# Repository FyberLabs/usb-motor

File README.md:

# usb-motor driver
Variation on the [Small Multicell USB Type C Charger](https://hackaday.io/project/85465-small-multicell-usb-type-c-charger), but with a specific purpose of making USB powered tools.
There will be a brushless version eventually and a few other application variations.
It supports a variety of rechargeable batteries and 1-4 cells depending on the solder bridge configuration.

For right now it has a single power/action button that can turn on/off, change speed, and reverse direction.
A capacitive trigger or other more precise control can be added.
There is also a reset button that can be removed after development.

These boards should 'mostly' stack in a 1x1.5" space with only a few wiring problems between them.
This design has excessive FET control and filtering which can be reduced.
Ideally, the design should fit on a single 1x1.5" board when developed for a specific application.

[Submitted gerbers to oshpark](https://oshpark.com/shared_projects/w56T8NJs])

[Assembly BOM](http://htmlpreview.github.com/?https://github.com/FyberLabs/usb-motor/blob/master/bom/ibom.html)
Generated By [InteractiveHtmlBom](https://github.com/openscopeproject/InteractiveHtmlBom)  

GPL licensed firmware will be coming for the CCG3.  I expect to use stock TI firmware for TI chips.

Notes:
* There will be bugs in the hardware and eventually they will hopefully be found and 'fixed.
* There are many solderbridges to disable FET controls and select cell counts as necessary.
* The CC 5V line on CCG3 should be routed or the 3v3 supply made 5V to fully enable a powerbank/OTG capabilities.
* Initial testing of some of the boards, so some logic may be incorrect.
* Developed with extra small designator silkscreen fonts which are likely to fail most PCB processes.  
(They are not that important to my build process, and usually make a mess of the silkscreen either way.)
* First panel attempted through oshpark  
(Usually I remove edge lines on mousebites for other fabs, though this variation does make copper zones in KiCAD work better.)

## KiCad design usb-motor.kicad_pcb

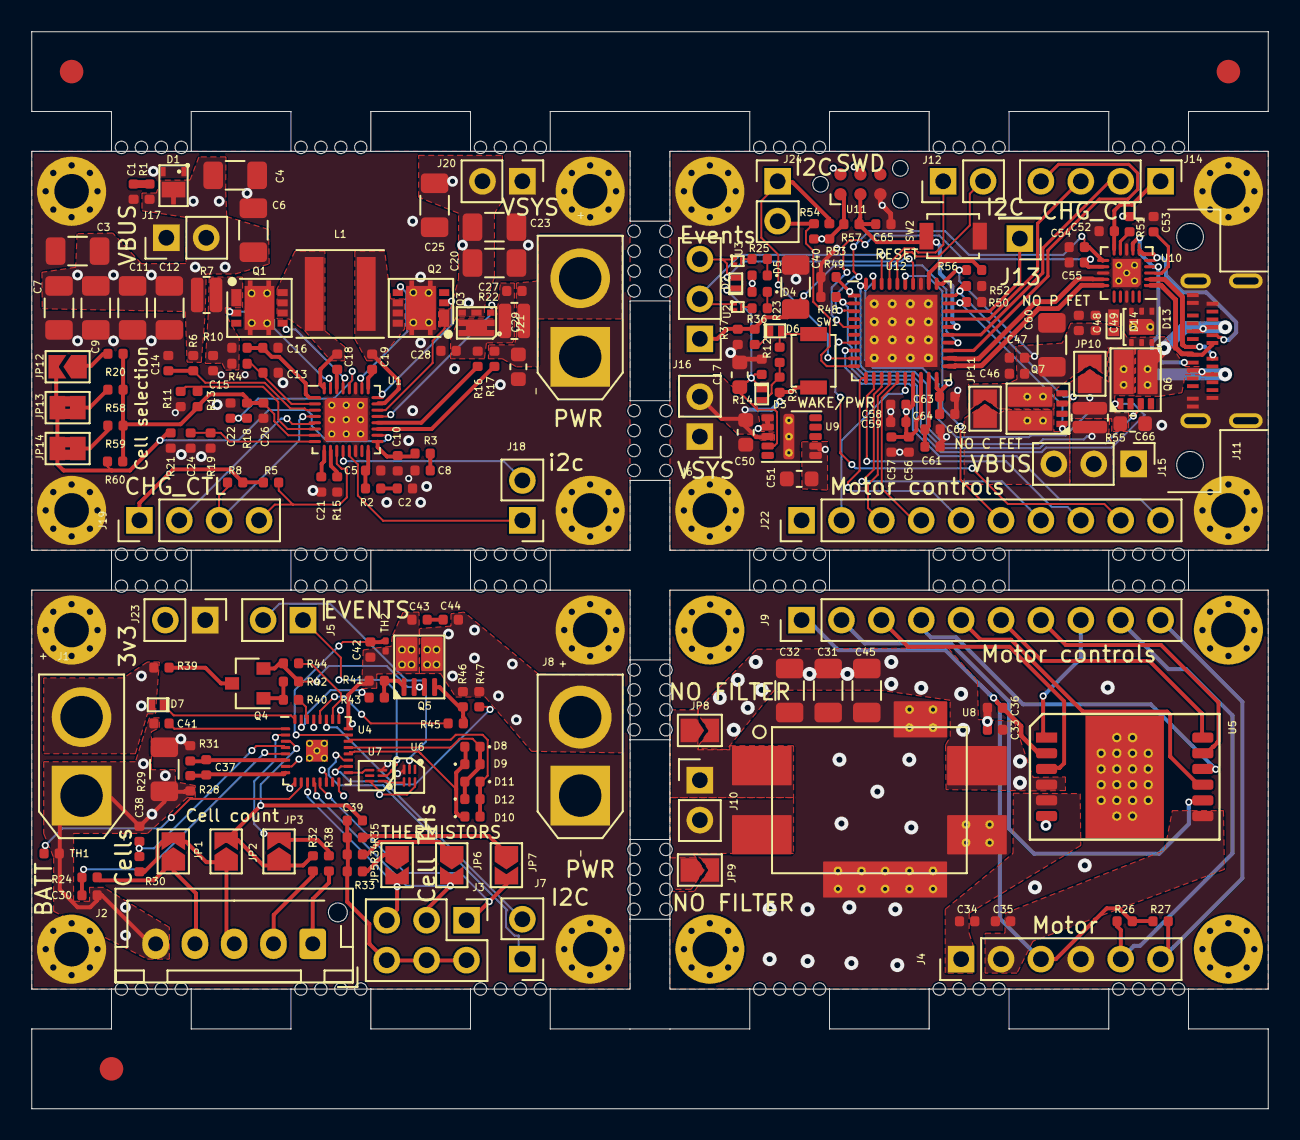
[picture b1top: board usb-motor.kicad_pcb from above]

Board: 4 copper layers, 78.7 x 68.6 mm, 252 parts (0 on the bottom side), 128 nets.

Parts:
C1, C26, C28, C52, C57, C58, C61, C63: 1uF; C_0402_1005Metric
C2: 1800pF; C_0402_1005Metric
C3, C4, C6, C7, C9, C11, C12, C20, C23, C25, C31, C32, C40, C45: 22uF; C_1206_3216Metric
C5: 33pF; C_0402_1005Metric
C8: 680pF; C_0402_1005Metric
C10: 15pF; C_0402_1005Metric
C13, C14: 0.033uF; C_0402_1005Metric
C15, C46, C47, C48, C49: 0.01uF; C_0402_1005Metric
C16: 0.47uF; C_0402_1005Metric
C17, C29, C50: 10uF; C_0603_1608Metric
C18, C19: 0.047uF; C_0402_1005Metric
C21, C24: 100pF; C_0402_1005Metric
C22, C41: 2.2uF; C_0402_1005Metric
C27, C30, C33, C36, C37, C38, C39, C42, C43, C53, C56, C59, C62, C64, C65: 0.1uF; C_0402_1005Metric
C34, C35: 27nF; C_0402_1005Metric
C44: 0.22uF; C_0402_1005Metric
C51: 22uF+ 6.3V; C_0603_1608Metric
C54, C55: 390pF; C_0402_1005Metric
C60: 10uF; C_1206_3216Metric
C66: 1uF; C_0603_1608Metric
D1: ESDA22P150-1U3M; QFN-3 (ESDA22P150-1U3M)
D2, D3, D6, D7: BAS40LP-7; D_402
D4: VLMG1500-GS08; LED_0402_1005Metric
D5: VLMO1500-GS08; LED_0402_1005Metric
D8, D9, D10, D11, D12: VLMB1500-GS08; LED_0402_1005Metric
D13: TVS2200; TVS2200-DRV0006A-WSON-2x2
D14: NSR20F30NXT5G; DSN2(0603)
FID1, FID2, FID3: Fiducial; Fiducial_1.5mm_Mask3mm
H1, H2, H3, H4, H5, H6, H7, H8, H9, H10, H11, H12, H13, H14, H15, H16: M; MountingHole_2.2mm_M2_Pad_Via
J1: BATT; AMASS_XT30U-M_1x02_P5.0mm_Vertical
J2: Cells; JST_XH_B5B-XH-AM_1x05_P2.50mm_Vertical
J3: Cell THs; PinHeader_2x03_P2.54mm_Vertical
J4: Motor; PinHeader_1x06_P2.54mm_Vertical
J5: EVENTS; PinHeader_1x02_P2.54mm_Vertical
J6, J20: VSYS; PinHeader_1x02_P2.54mm_Vertical
J7, J12, J24: I2C; PinHeader_1x02_P2.54mm_Vertical
J8: PWR; AMASS_XT30U-F_1x02_P5.0mm_Vertical
J9, J22: Motor controls; PinHeader_1x10_P2.54mm_Vertical
J10: Power; PinHeader_1x02_P2.54mm_Vertical
J11: USB_C_Receptacle; USB_C_Receptacle_Amphenol_124018792112A
J13: xpins; PinHeader_1x01_P2.54mm_Vertical
J14, J19: CHG_CTL; PinHeader_1x04_P2.54mm_Vertical
J15: VBUS; PinHeader_1x03_P2.54mm_Vertical
J16: Events; PinHeader_1x03_P2.54mm_Vertical
J17: VBUS; PinHeader_1x02_P2.54mm_Vertical
J18: i2c; PinHeader_1x02_P2.54mm_Vertical
J21: PWR; AMASS_XT30U-M_1x02_P5.0mm_Vertical
J23: 3v3; PinHeader_1x02_P2.54mm_Vertical
JP1, JP2, JP3, JP5, JP6, JP7: SolderJumper_2_Open; SolderJumper-2_P1.3mm_Open_TrianglePad1.0x1.5mm
JP8, JP9: NO FILTER; SolderJumper-2_P1.3mm_Open_TrianglePad1.0x1.5mm
JP10: NO P FET; SolderJumper-2_P1.3mm_Open_TrianglePad1.0x1.5mm
JP11: NO C FET; SolderJumper-2_P1.3mm_Open_TrianglePad1.0x1.5mm
JP12: 4th; SolderJumper-2_P1.3mm_Open_TrianglePad1.0x1.5mm
JP13: 3rd; SolderJumper-2_P1.3mm_Bridged2Bar_Pad1.0x1.5mm
JP14: 2nd; SolderJumper-2_P1.3mm_Bridged2Bar_Pad1.0x1.5mm
L1: 2.2uH; L_Coilcraft_XAL5030
MOU1, MOU2, MOU3, MOU4, MOU5, MOU6, MOU7, MOU8, MOU9, MOU10, MOU11, MOU12, MOU13, MOU14, MOU15, MOU16, MOU17, MOU18, MOU19, MOU20, MOU21, MOU22, MOU23, MOU24, MOU25, MOU26, MOU27, MOU28, MOU29, MOU30, MOU31, MOU32: Mousebite; mousebites
Q1, Q2: CSD87333Q3D
Q3: FDMA6676PZ; MicroFET
Q4: FDN358P; SOT-23
Q5: CSD87313DMS
Q6, Q7: CSD87503Q3E
R1: 2.2 0.5W; R_0402_1005Metric
R2: 40.2k; R_0402_1005Metric
R3, R23, R25, R26, R27, R33, R34, R35, R36, R47: 10.0k; R_0402_1005Metric
R4, R6: 4.99; R_0402_1005Metric
R5, R8: 3.83k; R_0402_1005Metric
R7, R22, R55: 10m; KRL2012E(0508)
R9, R12: 270k; R_0402_1005Metric
R10: 1.0; R_0402_1005Metric
R11, R13, R14, R21, R37, R51: 100k; R_0402_1005Metric
R15: 30k; R_0402_1005Metric
R16, R17, R18: 10; R_0402_1005Metric
R19: 137k; R_0402_1005Metric
R20: 56-57k; R_0402_1005Metric
R24, R28, R30, R31, R32, R38, R44, R56: 100; R_0402_1005Metric
R29: 0.001; R_1206_3216Metric
R39: 300; R_0402_1005Metric
R40, R43, R45: 5.1k; R_0402_1005Metric
R41, R42, R46, R48, R49, R50, R52: 10.0M; R_0402_1005Metric
R53, R54: 2.2k; R_0402_1005Metric
R57: 4.7k; R_0402_1005Metric
R58: 169k; R_0402_1005Metric
R59: 280k; R_0402_1005Metric
R60: 300k; R_0402_1005Metric
SW1: WAKE/PWR; SW_SPST_B3U-1000P
SW2: RESET; SW_SPST_B3U-1000P
TH1: 103; R_0402_1005Metric
TH2: 10.0k; R_0201_0603Metric
U1: BQ25713(B); QFN-32_EP2.8_4x4_Pitch0.4mm
U2, U3: CSD15380F3; PICOSTAR (YJM)
U4: BQ4050R; QFN-32_EP1.4_4x4_Pitch0.4mm
U5: IFX9201SG; PG-DSO-12-17
U6: SN74LVC1G14D; TI-DSF0006A-SON-5P-SN74xx
U7: SN74LVC1G08D; TI-DSF0006A-SON-5P-SN74xx
U8: BNX02x
U9: LMZM23601V3; Texas_SIL0010A_MicroSiP-10-1EP_3.8x3mm_P0.6mm_EP0.7x2.9mm_T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
U10: TPD6S300A; QFN-20_EP1.8_3x3_Pitch0.4mm
U11: SWD; Tag-Connect_TC2030-IDC-NL_2x03_P1.27mm_Vertical
U12: CYPD3123-40LQXIT; QFN-40_EP_6x6_Pitch0.5mm

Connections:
+3V3: C51.2, C63.2, C64.2, D4.2, D5.2, J23.2, R51.2, U6.5, U7.5, U9.6, U9.7, U12.20
-BATT: C30.1, C38.1, C39.1, C41.1, J1.1, J2.5, J3.2, J3.4, J3.6, R28.2, R29.2, R33.1, R34.1, R35.1, TH1.2, U4.7, U4.9, U4.14, U4.16, U4.25, U4.29, U4.33
/4 Cell Charger/1c: J2.4, JP1.1, R24.2
/4 Cell Charger/2c: J2.3, JP1.2, JP2.1, R30.2
/4 Cell Charger/3c: J2.2, R32.2
/4 Cell Charger/BBAT: D7.1, U4.32
/4 Cell Charger/C43-44: C43.2, C44.1
/4 Cell Charger/CHG: R43.1, U4.31
/4 Cell Charger/DSG: R45.1, U4.28
/4 Cell Charger/JP5: JP5.1, R33.2
/4 Cell Charger/JP6: JP6.1, R34.2
/4 Cell Charger/JP7: JP7.1, R35.2
/4 Cell Charger/LEDA: D8.2, D9.1, D10.1, U4.20
/4 Cell Charger/LEDB: D8.1, D9.2, D11.2, D12.1, U4.21
/4 Cell Charger/LEDC: D10.2, D11.1, D12.2, U4.22
/4 Cell Charger/PACK: R47.2, U4.27
/4 Cell Charger/PBI: C41.2, U4.1
/4 Cell Charger/PCHG: R40.2, U4.30
/4 Cell Charger/PTC: C42.1, TH2.1, U4.23
/4 Cell Charger/R39: Q4.3, R39.1
/4 Cell Charger/R40: Q4.1, R40.1, R42.1
/4 Cell Charger/R43: Q5.1, R41.1, R43.2
/4 Cell Charger/R45: Q5.4, R45.2, R46.1
/4 Cell Charger/SRN: C37.1, R31.1, U4.6
/4 Cell Charger/SRP: C37.2, R28.1, U4.8
/4 Cell Charger/TS1: TH1.1, U4.10
/4 Cell Charger/TS2: J3.5, JP5.2, U4.11
/4 Cell Charger/TS3: J3.3, JP6.2, U4.12
/4 Cell Charger/TS4: J3.1, JP7.2, U4.13
/4 Cell Charger/VC1: C30.2, R24.1, U4.5
/4 Cell Charger/VC2: C38.2, R30.1, U4.4
/4 Cell Charger/VC3: C39.2, JP2.2, JP3.1, R32.1, U4.3
/4 Cell Charger/VC4: JP3.2, R38.1, U4.2
/4 Cell Charger/VCCQ: Q4.2, Q5.2, Q5.3, R42.2, R44.2
/4 Cell Charger/VCCcell: R44.1, U4.26
/4 Cell Charger/~DISP: U4.17, U7.4
/4 Cell Charger/~SW_SIG: U6.4, U7.1
/6-36V: C42.2, C43.1, D7.2, J1.2, J2.1, J10.1, JP8.1, Q5.8, R38.2, R39.2, R41.2, TH2.2, U4.24, U8.B
/BAT_OUT: C27.2, C29.1, C44.2, J8.2, J21.2, Q5.5, R17.1, R22.1, R46.2, R47.1
/Brushed 12V Motor/36V: C31.2, C32.1, C33.1, C45.2, JP8.2, U5.4, U8.CB
/Brushed 12V Motor/GNDF: C31.1, C32.2, C33.2, C34.2, C35.2, C36.2, C45.1, J4.4, JP9.2, U5.6, U8.CG
/Brushed 12V Motor/M1: C34.1, J4.1, U5.5
/Brushed 12V Motor/M2: C35.1, J4.2, U5.7
/CHRG_OK: J14.3, J19.3, R8.1, U1.4, U12.27
/CSN: J9.5, J22.5, U5.9, U12.11
/DIR: J9.8, J22.8, U5.1, U11.4, U12.12
/DIS: J9.7, J22.7, U5.11, U11.2, U12.13
/EN_OTG: J14.2, J19.2, U1.5, U12.25
/GPIO13: J13.1, U12.28
/PROCHOT: J14.4, J19.4, R5.1, U1.11, U12.23
/PWM: J9.6, J22.6, U5.12, U12.35
/SCK: J9.4, J22.4, U5.10, U12.15
/SCL: J7.1, J18.1, J24.1, R53.2, U1.13, U4.19, U12.9
/SDA: J7.2, J18.2, J24.2, R54.2, U1.12, U4.18, U12.10
/SENSA: J4.5, J9.9, J22.9, R26.2, U12.7
/SENSB: J4.6, J9.10, J22.10, R27.2, U12.8
/SI: J9.2, J22.2, U5.8, U12.16
/SNK_EVENT: D2.2, J5.1, J16.3, U3.1, U7.2, U12.34
/SO: J9.3, J22.3, U5.3, U12.14
/SW_SIG: C40.2, J5.2, J16.1, R36.2, R37.1, U6.2, U12.24
/USB Buck Boost/ACN: C13.1, R4.1, U1.2
/USB Buck Boost/ACP: C14.1, R6.1, U1.3
/USB Buck Boost/CELL_PREZ: JP12.2, JP13.2, JP14.2, R21.1, R60.2, U1.18
/USB Buck Boost/COMP1: C5.1, R2.2, U1.16
/USB Buck Boost/COMP1T: C2.1, R2.1
/USB Buck Boost/COMP2: C10.1, R3.2, U1.17
/USB Buck Boost/COMP2TT: C8.1, R3.1
/USB Buck Boost/HIDRV1: Q1.3, U1.31
/USB Buck Boost/HIDRV2: Q2.3, U1.24
/USB Buck Boost/IADPT: C24.1, R19.1, U1.8
/USB Buck Boost/IBAT: C21.1, U1.9
/USB Buck Boost/ILIM: R11.1, R13.1, U1.6
/USB Buck Boost/JP12: JP12.1, R20.2
/USB Buck Boost/JP13: JP13.1, R58.2
/USB Buck Boost/JP14: JP14.1, R59.2
/USB Buck Boost/LODRV1: Q1.5, U1.29
/USB Buck Boost/LODRV2: Q2.5, U1.26
/USB Buck Boost/PSYS: R15.1, U1.10
/USB Buck Boost/REGN: C22.1, R18.2, U1.28
/USB Buck Boost/SRN: R17.2, U1.19
/USB Buck Boost/SRP: R16.2, U1.20
/USB Buck Boost/SRP_R: C27.1, C28.1, Q3.1, Q3.2, Q3.5, Q3.6, Q3.8, R16.1, R22.2
/USB Buck Boost/SW1: C18.1, L1.1, Q1.6, Q1.7, Q1.8, U1.32
/USB Buck Boost/SW2: C19.1, L1.2, Q2.6, Q2.7, Q2.8, U1.23
/USB Buck Boost/TST1: C18.2, U1.30
/USB Buck Boost/TST2: C19.2, U1.25
/USB Buck Boost/VBUS_D: C1.2, R1.1
/USB Buck Boost/VBUS_IN: C16.1, R10.2, U1.1
/USB Buck Boost/VBUS_VIN: C15.1, Q1.1, Q1.2, R4.2, R7.1, R10.1
/USB Buck Boost/VDDA: C26.1, R13.2, R18.1, R20.1, R58.1, R59.1, R60.1, U1.7
/USB Buck Boost/~BATDRV: Q3.3, U1.21
/USB PD/CC1: C55.2, U10.12, U12.5
/USB PD/CC2: C54.1, U10.11, U12.3
/USB PD/C_CC1: J11.A5, U10.4, U10.7
/USB PD/C_CC2: J11.B5, U10.5, U10.6
/USB PD/D4: D4.1, R23.1
/USB PD/D5: D5.1, R25.1
/USB PD/D6: D6.1, R36.1
/USB PD/DN: J11.A7, J11.B7, U10.2
/USB PD/DP: J11.A6, J11.B6, U10.1
/USB PD/H_DN: U10.14, U12.22
/USB PD/H_DP: U10.15, U12.21
/USB PD/OC: C66.2, JP10.1, Q6.8, R55.2, U12.39
/USB PD/R23: R23.2, U2.3
/USB PD/R25: R25.2, U3.3
/USB PD/SRC_EVENT: J16.2, U2.1, U12.38
/USB PD/SW: D6.2, R12.1, SW1.2
/USB PD/SW_EN: D3.2, R9.2, R12.2
/USB PD/SW_S_EN: C17.1, D2.1, D3.1, R14.1, U9.4
/USB PD/VBIAS: C53.2, U10.3
/USB PD/VBUS_C_C0: Q7.3, R52.2, U12.30
/USB PD/VBUS_C_C1: Q7.1, R50.2, U12.29
/USB PD/VBUS_P_C0: Q6.1, R48.2, U12.2
/USB PD/VBUS_P_C1: Q6.3, R49.2, U12.1
/USB PD/VCCD: C61.2, C62.2, U12.19
/USB PD/VDISCHG: R56.2, U12.32
/USB PD/XRES: C65.2, R57.1, SW2.1, U11.3, U12.26
/USB PD/~FLT: R51.1, U10.9
/VBUS: C3.1, C4.1, C6.1, C7.1, C9.1, C11.1, C12.1, D1.1, J15.2, J17.2, R1.2, R6.2, R7.2, R55.1, U12.40
/VBUS_C: J15.3, JP11.1, Q7.8
/VDDD: C36.1, C52.2, C56.2, C57.2, C58.2, C59.2, J4.3, J9.1, J14.1, J19.1, J22.1, R5.2, R8.2, R26.1, R27.1, R53.1, R54.1, R57.2, U5.2, U10.10, U11.1, U12.17, U12.18
/VSYS: C20.1, C23.1, C25.1, C50.2, J6.2, J20.2, Q2.1, Q2.2, Q3.4, Q3.7, R9.1, SW1.1, U1.22, U9.3
/X_SCL: J12.1, U12.37
/X_SDA: J12.2, U12.36
GND: C1.1, C2.2, C3.2, C4.2, C5.2, C6.2, C7.2, C8.2, C9.2, C10.2, C11.2, C12.2, C13.2, C14.2, C15.2, C16.2, C17.2, C20.2, C21.2, C22.2, C23.2, C24.2, C25.2, C26.2, C28.2, C29.2, C40.1, C46.1, C47.1, C48.1, C49.1, C50.1, C51.1, C52.1, C53.1, C54.2, C55.1, C56.1, C57.1, C58.1, C59.1, C60.1, C61.1, C62.1, C63.1, C64.1, C65.1, C66.1, D1.2, D13.2, D14.2, H1.1, H2.1, H3.1, H4.1, H5.1, H6.1, H7.1, H8.1, H9.1, H10.1, H11.1, H12.1, H13.1, H14.1, H15.1, H16.1, J6.1, J8.1, J10.2, J11.A1, J11.A12, J11.B1, J11.B12, J11.S1, J15.1, J17.1, J20.1, J21.1, J23.1, JP9.1, Q1.9, Q2.9, R11.2, R14.2, R15.2, R19.2, R21.2, R29.1, R31.2, R37.2, R48.1, R49.1, R50.1, R52.1, SW2.2, U1.14, U1.27, U1.33, U2.2, U3.2, U6.3, U7.3, U8.PSG, U9.1, U9.2, U9.11, U10.8, U10.13, U10.18, U10.21, U11.5, U12.33, U12.41
unnamed: Q6.2, Q6.4
unnamed: Q7.2, Q7.4
PRI_HI: C46.2, C47.2, C48.2, C49.2, C60.2, D13.1, D14.1, J11.A4, J11.A9, J11.B4, J11.B9, JP10.2, JP11.2, Q6.5, Q7.5, R56.1, U12.31

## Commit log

2019-09-06 initial public commit
2019-09-06 Initial README
2019-09-07 added some design notes
2019-10-28 Post fab edits for assembly
2019-10-28 Add assembly bom link
2019-10-28 add testing note file for design improvements
2019-10-28 fix cells dup name
2019-11-18 post fab error fixes, brushed motor needs refabbed.
